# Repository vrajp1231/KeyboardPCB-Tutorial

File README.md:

# KeyboardPCB-Tutorial
Following a Tutorial to create a Keyboard PCB

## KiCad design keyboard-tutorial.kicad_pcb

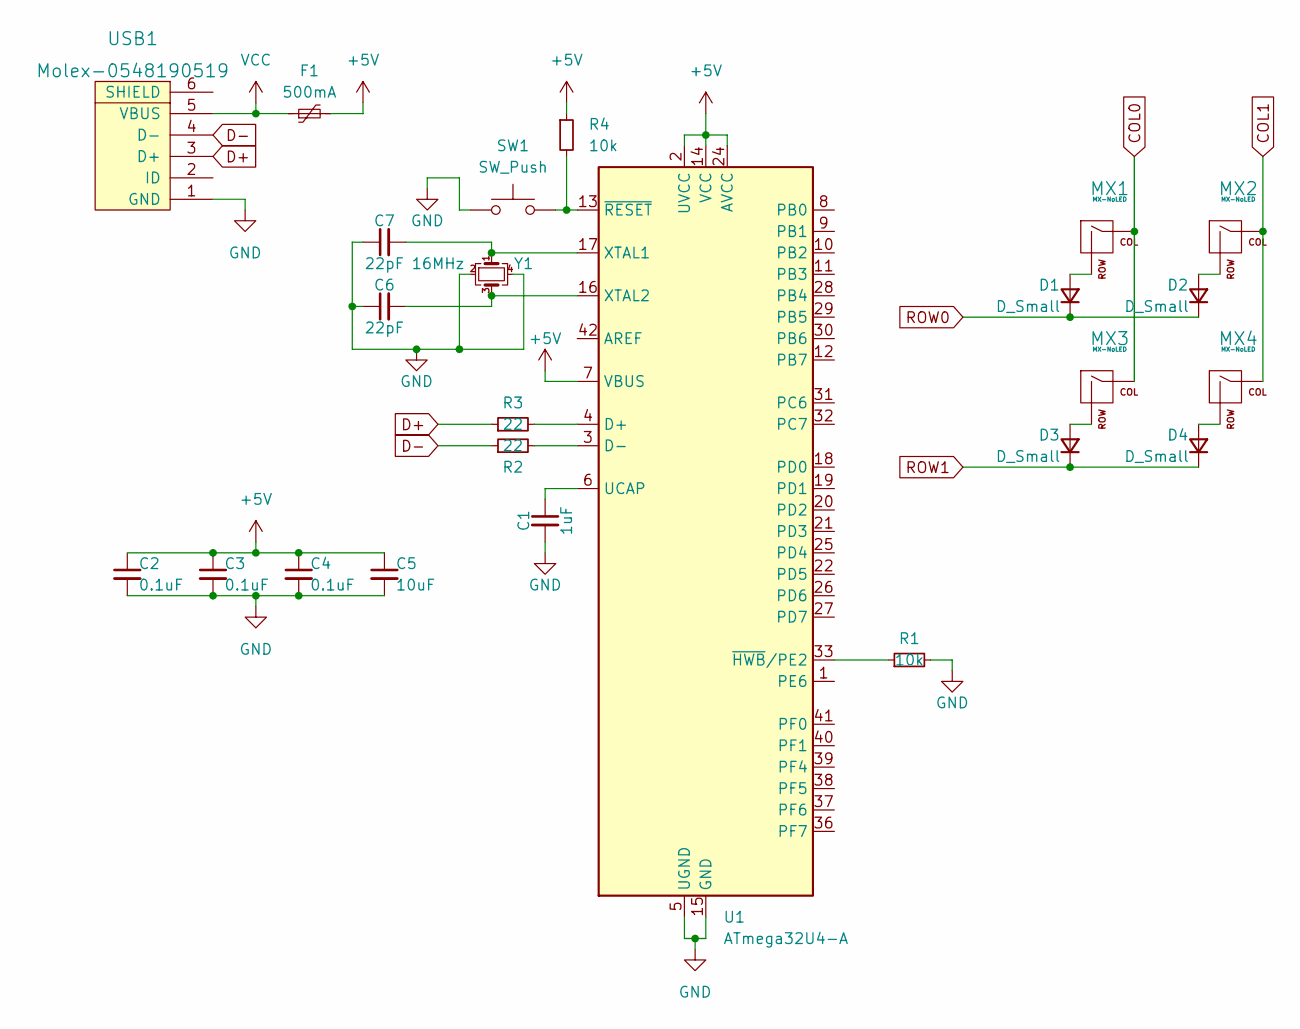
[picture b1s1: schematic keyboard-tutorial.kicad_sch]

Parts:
C1: 1uF; C_0805_2012Metric
C2, C3, C4: 0.1uF; C_0805_2012Metric
C5: 10uF; C_0805_2012Metric
C6, C7: 22pF; C_0805_2012Metric
D1, D2, D3, D4: D_Small; D_SOD-123
F1: 500mA; Fuse_1206_3216Metric
MX1, MX2, MX3, MX4: MX-NoLED; MX-1U-NoLED
R1, R4: 10k; R_0805_2012Metric
R2, R3: 22; R_0805_2012Metric
SW1: SW_Push; SKQG-1155865
U1: ATmega32U4-A; TQFP-44_10x10mm_P0.8mm
USB1: Molex-0548190519
Y1: 16MHz; Crystal_SMD_3225-4Pin_3.2x2.5mm

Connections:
+5V: C2.1, C3.1, C4.1, C5.1, F1.2, R4.1, U1.2 (UVCC), U1.7 (VBUS), U1.14 (VCC), U1.24 (AVCC), U1.34 (VCC), U1.44 (AVCC)
COL0: MX1.1 (COL), MX3.1 (COL)
COL1: MX2.1 (COL), MX4.1 (COL)
D+: R3.1, USB1.3 (D+)
D-: R2.1, USB1.4 (D-)
GND: C1.2, C2.2, C3.2, C4.2, C5.2, C6.1, C7.1, R1.2, SW1.1, U1.5 (UGND), U1.15 (GND), U1.23 (GND), U1.35 (GND), U1.43 (GND), USB1.1 (GND), Y1.2, Y1.4
unnamed: C1.1, U1.6 (UCAP)
unnamed: C6.2, U1.16 (XTAL2), Y1.3
unnamed: C7.2, U1.17 (XTAL1), Y1.1
unnamed: D1.2 (A), MX1.2 (ROW)
unnamed: D2.2 (A), MX2.2 (ROW)
unnamed: D3.2 (A), MX3.2 (ROW)
unnamed: D4.2 (A), MX4.2 (ROW)
unnamed: R1.1, U1.33 (~HWB/PE2)
unnamed: R2.2, U1.3 (D-)
unnamed: R3.2, U1.4 (D+)
unnamed: R4.2, SW1.2, U1.13 (~RESET)
ROW0: D1.1 (K), D2.1 (K)
ROW1: D3.1 (K), D4.1 (K)
VCC: F1.1, USB1.5 (VBUS)

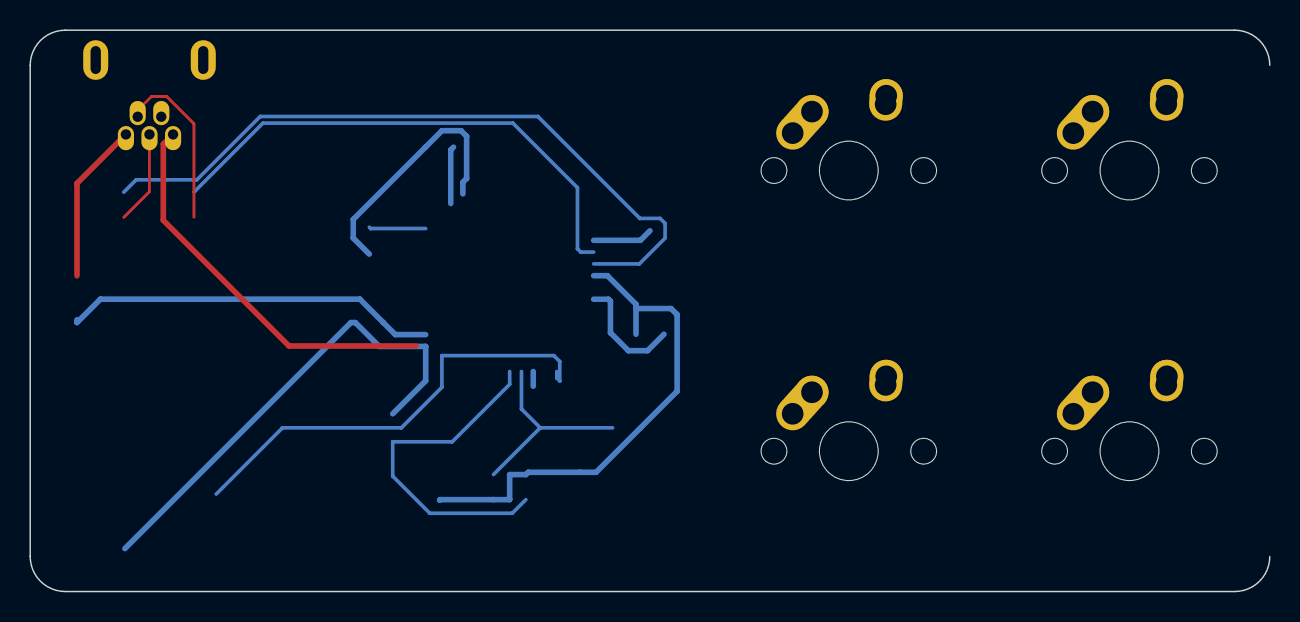
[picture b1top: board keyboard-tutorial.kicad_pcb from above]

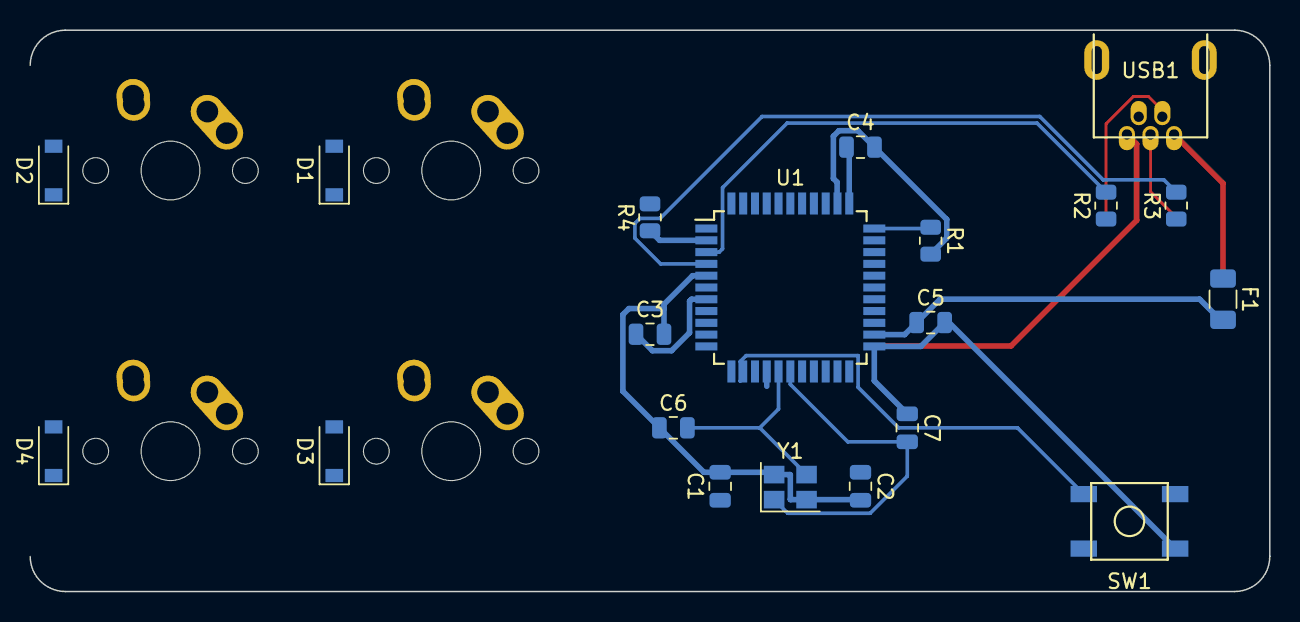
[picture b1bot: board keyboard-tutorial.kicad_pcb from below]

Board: 2 copper layers, 84.1 x 38.1 mm, 24 parts (20 on the bottom side), 20 nets.

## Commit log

2022-08-08 Initialize Project
2022-08-08 Add Submodules
2022-08-08 Add footprint libraries
2022-08-09 Starting Tracing
2022-08-14 Post Tracing
